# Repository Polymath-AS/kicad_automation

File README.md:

# KiCad 10 MCP Automation

This repository provides a reproducible Docker runtime for agent-driven KiCad work:

```text
Codex
  -> kicad-mcp-pro over Streamable HTTP
  -> KiCad 10 IPC / kipy
  -> pcbnew running under Xvfb

kicad-cli
  -> ERC, DRC, exports, validation
```

## Quick Start

After cloning, start the KiCad container and Codex together:

```powershell
.\tools\kicad-docker.ps1 start
```

The first run builds the Docker image, waits for the MCP endpoint, and then opens Codex. No token
setup is required. Docker Desktop must be installed and running.

Running plain `codex` is also safe: the KiCad MCP server is optional during Codex startup, so an
unavailable container no longer prevents the session from opening. Start the container and open a
new Codex session when you need KiCad tools.

## Build

```powershell
docker compose build
```

The image pins:

- `ghcr.io/inti-cmnb/kicad10_auto:1.9.0`, which ships KiCad `10.0.4` and the KiCad automation tool bundle.
- `kicad-mcp-pro==3.34.0`, installed in `/opt/kicad-mcp-pro`.

## Run

```powershell
docker compose up kicad
```

By default this opens `tests/fixtures/kicad-project/minimal.kicad_pcb`. To run against another mounted project:

```powershell
$env:KICAD_ENTRYPOINT_PROJECT = "CAD/my-board/my-board.kicad_pcb"
docker compose up kicad
```

The project is mounted at `/workspace`. Runtime sockets and logs live under `/runtime`; KiCad config is under `/config`; caches are under `/cache`.

The PowerShell wrapper validates the selected project on the host before Compose starts. A
complete target must resolve to matching `.kicad_pro`, `.kicad_sch`, and `.kicad_pcb` files under
`-ProjectRoot`. The host project root is mounted at `/workspace`, so the same resolved target is
passed to KiCad as `/workspace/<relative-project-path>`. This catches a stale selection or a
different mount before Docker validation runs; it does not recreate missing projects.

For example, validate a project from the same host root used by the live service with:

```powershell
.\tools\kicad-docker.ps1 validate tests/fixtures/kicad-project/minimal --erc --drc
```

If Docker itself fails, the wrapper preserves sanitized Compose output under
`.kicad-automation/compose-failures/` and reports the failure class. Authentication tokens are
not written to those reports.

MCP Pro is published only to host loopback:

```text
http://127.0.0.1:3334/mcp
```

Codex reads the project-scoped `.codex/config.toml` only for a trusted project. Its static
Authorization header matches the non-secret development token used by Compose. The service is
published only on host loopback, and a missing service does not prevent Codex from starting.
Verify the connection with `codex mcp list` and the `/mcp` command in the Codex interface.

For automation, diagnostics, and tools that are not visible in a client's cached catalog, use the
checked-in MCP client instead of constructing HTTP requests by hand:

```powershell
.\tools\kicad-mcp.ps1 wait
.\tools\kicad-mcp.ps1 list
.\tools\kicad-mcp.ps1 schema pcb_get_board_summary
.\tools\kicad-mcp.ps1 call pcb_get_board_summary --arguments '{}'
```

`list` annotates the live response with stable backend/availability metadata. Use
`.\tools\kicad-mcp.ps1 catalog` for the complete discoverable superset, including tools that are
currently unavailable in a selected upstream operating mode. Discoverability does not grant write
permission.

`--arguments` also accepts `@path/to/arguments.json`, which avoids shell-quoting problems for
larger payloads. Connection settings can be overridden with `KICAD_MCP_URL` and
`KICAD_MCP_AUTH_TOKEN`.

Codex project config example:

```toml
[mcp_servers.kicad]
url = "http://127.0.0.1:3334/mcp"
http_headers = { Authorization = "Bearer kicad-automation-local-dev-token-change-me-2026" }
required = false
startup_timeout_sec = 60
tool_timeout_sec = 120
default_tools_approval_mode = "writes"
```

## Generate a Project

MCP Pro exposes `kicad_create_new_project` in the default write-enabled profile. Generate a
complete KiCad project directory under the mounted `/workspace`; do not create a PCB-only file:

```text
my-board/
  my-board.kicad_pro
  my-board.kicad_sch
  my-board.kicad_pcb
```

The current runtime opens a board before starting MCP so that live IPC is ready. Bootstrap a new
project while the service is running against the fixture or another existing board, then restart
the service against the generated board:

```powershell
.\tools\kicad-docker.ps1 up `
  -ProjectRoot "C:\Users\fnk\Documents\KiCad\Projects" `
  -Target "my-board/my-board.kicad_pcb"
```

The generated project remains in the mounted host directory. After restarting, use MCP Pro for
inspection/editing and `validate-kicad --erc --drc` before continuing.

## MCP Surface

Use KiCad MCP Pro tool names directly. The default `builder` profile exposes the live PCB
workflow, including:

`kicad_get_server_info`, `kicad_get_project_info`, `kicad_get_version`, `pcb_get_board_summary`,
`pcb_get_footprints`, `pcb_get_nets`, `pcb_get_tracks`, `pcb_get_shapes`,
`pcb_visual_qa`, `pcb_visual_review`, `pcb_visual_history`, `pcb_visual_get`,
`pcb_visual_compare`, `pcb_move_component`, `pcb_move_footprint`,
`pcb_route_trace`, and `pcb_save`.

For iterative visual review, capture with `pcb_visual_review`, browse with `pcb_visual_history`,
zoom retained SVGs with `pcb_visual_get`, and compare captures with `pcb_visual_compare`.
Captures return native PNG image content and keep all SVGs, PNGs, frozen source copies, and
hash/version manifests under the active project's `output/image-review/<review-id>/`.
Open `output/image-review/index.html` to see progress. Nothing is automatically pruned.
These tools write review artifacts, not the design. Explicitly `pcb_save` first for live changes;
use `board_path` and `expected_sha256` for isolated candidates. See the
[review loop, API, retention guarantees, and setup](docs/PCB_VISUAL_REVIEW.md).

The default profile is `builder` with `KICAD_MCP_OPERATING_MODE=write` and file-backed schematic
support. It exposes the stable project-building surface needed to create and inspect schematics,
synchronize and edit a live PCB, route, save, and run ERC/DRC without restarting the service.
Use `manufacturing` or another specialized upstream profile only for workflows outside that
design surface.

Schematic support is split deliberately:

- KiCad 10.0.4 does not provide a verified schematic-editor IPC surface. The official IPC
  documentation describes KiCad 9/10 IPC as GUI-only and PCB-oriented; the installed `kipy`
  schematic class is marked KiCad 11-only and is incompatible with the bundled KiCad 10
  protobufs. The runtime therefore does not start Eeschema as a false readiness signal.
- The default `builder` profile exposes MCP Pro's supported file-backed schematic tools with
  `KICAD_MCP_SCHEMATIC_MODE=file_backed`. Their responses identify `Source: file-backed`.
- `KICAD_MCP_SCHEMATIC_MODE=live` fails early with the exact unsupported-stack diagnosis. It is
  reserved for a future verified KiCad 11+ IPC configuration; it does not silently fall back to
  file editing.

The project-scoped Codex allowlist includes the supported file-backed schematic inspection tools;
restart Codex after changing the server profile so its tool catalog is refreshed.

The integration test records `liveSchematicContext`, `liveSchematicRead`, schematic tool
exposure, and the backend identified by the schematic read. Set
`KICAD_TEST_SCHEMATIC_LIVE=1` only when testing a stack that is expected to provide a real live
schematic document; the test fails if MCP reports a file-backed fallback.

The pinned KiCad 10 pad-to-pad regression is opt-in because upstream exposes
`route_from_pad_to_pad` only in experimental write mode. Run it against a disposable two-pad
project with `KICAD_MCP_OPERATING_MODE=experimental` and `KICAD_TEST_PAD_TO_PAD=1`;
`scripts/pad_to_pad_regression.py` resolves named pads, routes and saves them, reads the live board
back, checks net assignment, and runs DRC. It reports pre-existing fixture warnings separately
from unconnected-route failures.

## Validate

`kicad-cli` is the validation/export authority. The primary entry point is:

```powershell
docker compose run --rm kicad validate --project /workspace/tests/fixtures/kicad-project/minimal --erc --drc
docker compose run --rm kicad validate --project /workspace/CAD/my-board/my-board --all
```

The script supports ERC, DRC, Gerbers, drill files, schematic/PCB PDFs, and BOM export.
It emits a JSON result with separate ERC and DRC statuses, report paths, violation counts, the
captured `kicad-cli` log, and an overall status. `clean` is used only when both requested checks
ran and produced no violations. Missing project files, validator execution errors, and reported
ERC/DRC violations return distinct nonzero outcomes.

## Preferred KiCadRoutingTools placement and routing

The separate routing image exposes conservative placement refinement plus `route`, `diff`, and
`planes` as validated candidate jobs through CLI and MCP. After initial MCP placement, save the
unrouted board and use the candidate placer's bounded moves to improve routability. Lock
connectors, mounting parts, and RF/mechanical-critical parts, and provide reviewed placement
intent when available. KiCadRoutingTools is the preferred routing path; direct IPC traces remain
useful for previews and small reviewed fixes. The candidate service reads the source project
through a read-only mount, preserves the original rules for ERC/DRC, and never automatically
overwrites the live board.

Reviewed additive-track and placement candidates can be promoted explicitly through
`scripts/kicad_live_promotion.py` and `scripts/kicad_live_placement.py`. Promotion requires stale
source checks, save/reopen/readback, and post-mutation validation. Unsupported vias/removals and
unverifiable rollback fail closed; candidate generation itself remains non-mutating.

```powershell
.\tools\kicad-routing.cmd build
.\tools\kicad-routing.cmd doctor
.\tools\kicad-routing.cmd run routing-plans/smoke.json
```

The smoke fixture is expected to return `needs_review`: routing resolves its missing connection,
but two pre-existing footprint identifier warnings remain. Non-clean candidates return exit 1.
See [the detailed integration guide and remaining milestones](docs/KICAD_ROUTING_TOOLS.md)
for installation, MCP configuration, plans, evidence, review, limitations and tests.

## Test

```powershell
docker compose run --rm test
```

The integration path verifies KiCad 10.x, Xvfb, `DISPLAY`, pcbnew launch, IPC socket creation,
MCP Pro startup, MCP tool discovery, live PCB queries before and after save, project diagnostics,
schematic capability evidence when a schematic profile is selected, and separate clean ERC/DRC
results. It does not treat an Eeschema process that merely stays alive as proof of schematic IPC.

PowerShell convenience wrapper:

```powershell
.\tools\kicad-docker.ps1 build
.\tools\kicad-docker.ps1 test
.\tools\kicad-docker.ps1 validate tests/fixtures/kicad-project/minimal --erc --drc
```

On Windows hosts that enforce a restrictive PowerShell execution policy, use the checked-in
launchers instead of changing machine or user policy:

```bat
tools\kicad-docker.cmd start
tools\kicad-docker.cmd validate tests/fixtures/kicad-project/minimal --erc --drc
tools\kicad-mcp.cmd call pcb_get_board_summary
```

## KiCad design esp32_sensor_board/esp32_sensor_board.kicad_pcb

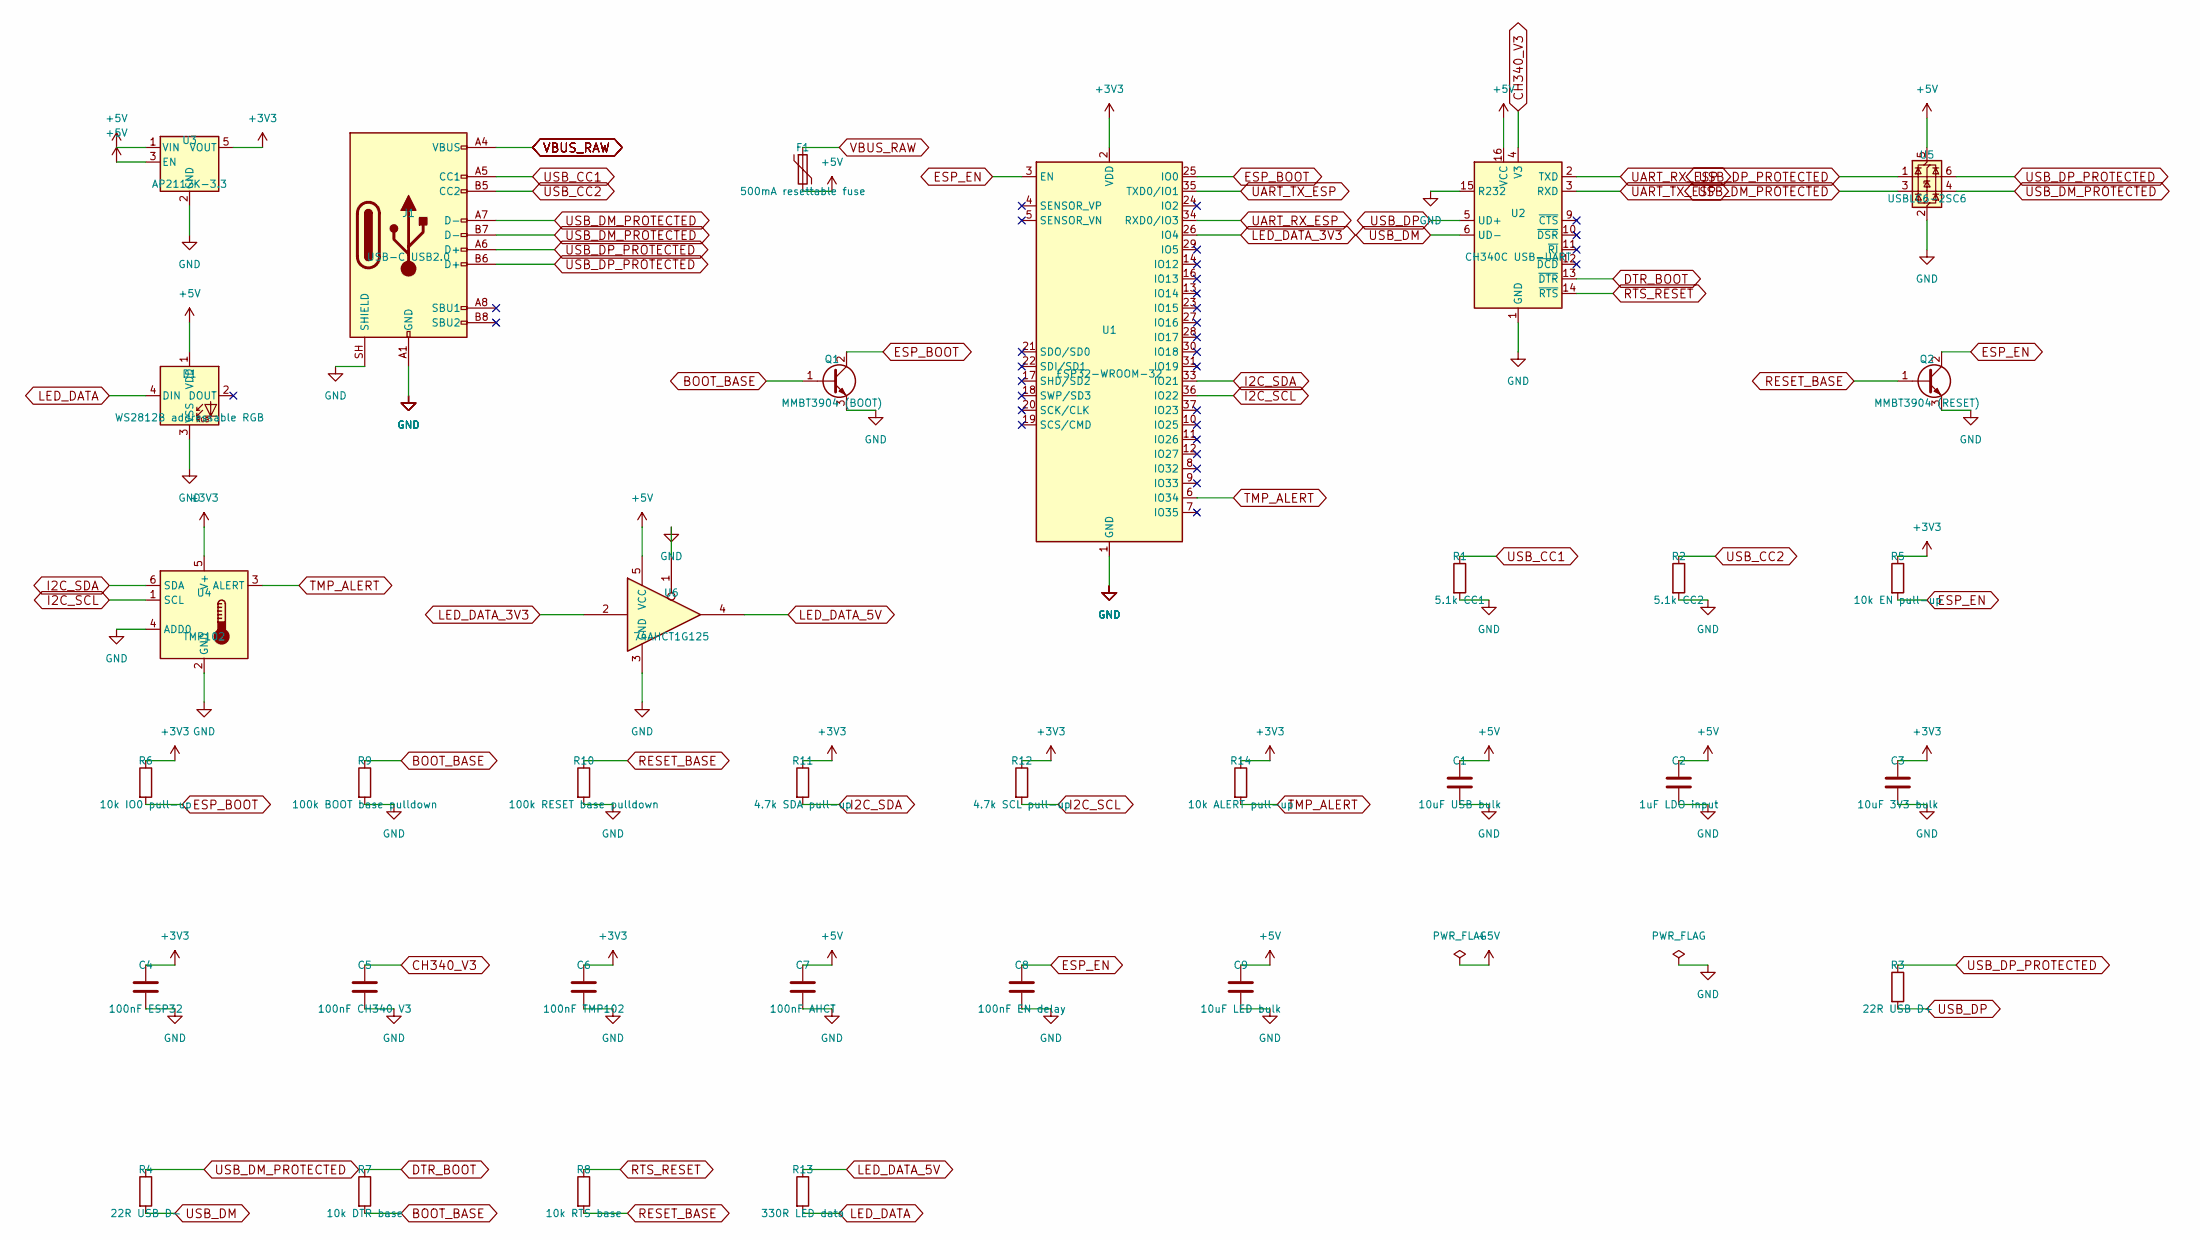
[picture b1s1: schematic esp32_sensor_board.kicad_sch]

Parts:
C1: 10uF USB bulk; C_1206_3216Metric
C2: 1uF LDO input; C_0603_1608Metric
C3: 10uF 3V3 bulk; C_1206_3216Metric
C4: 100nF ESP32; C_0603_1608Metric
C5: 100nF CH340 V3; C_0603_1608Metric
C6: 100nF TMP102; C_0603_1608Metric
C7: 100nF AHCT; C_0603_1608Metric
C8: 100nF EN delay; C_0603_1608Metric
C9: 10uF LED bulk; C_1206_3216Metric
D1: WS2812B addressable RGB; LED_WS2812B_PLCC4_5.0x5.0mm_P3.2mm
F1: 500mA resettable fuse; Fuse_1206_3216Metric
J1: USB-C USB2.0; USB_C_Receptacle_GCT_USB4105-xx-A_16P_TopMnt_Horizontal
Q1: MMBT3904 (BOOT); SOT-23
Q2: MMBT3904 (RESET); SOT-23
R1: 5.1k CC1; R_0603_1608Metric
R2: 5.1k CC2; R_0603_1608Metric
R3: 22R USB D+; R_0603_1608Metric
R4: 22R USB D-; R_0603_1608Metric
R5: 10k EN pull-up; R_0603_1608Metric
R6: 10k IO0 pull-up; R_0603_1608Metric
R7: 10k DTR base; R_0603_1608Metric
R8: 10k RTS base; R_0603_1608Metric
R9: 100k BOOT base pulldown; R_0603_1608Metric
R10: 100k RESET base pulldown; R_0603_1608Metric
R11: 4.7k SDA pull-up; R_0603_1608Metric
R12: 4.7k SCL pull-up; R_0603_1608Metric
R13: 330R LED data; R_0603_1608Metric
R14: 10k ALERT pull-up; R_0603_1608Metric
U1: ESP32-WROOM-32
U2: CH340C USB-UART; SOIC-16_3.9x9.9mm_P1.27mm
U3: AP2112K-3.3; SOT-23-5
U4: TMP102; SOT-563
U5: USBLC6-2SC6; SOT-23-6
U6: 74AHCT1G125; SOT-23-5

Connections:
+3V3: C3.1, C4.1, C6.1, R5.1, R6.1, R11.1, R12.1, R14.1, U1.2 (VDD), U3.5 (VOUT), U4.5 (V+)
+5V: C1.1, C2.1, C7.1, C9.1, D1.1 (VDD), F1.2, U2.16 (VCC), U3.1 (VIN), U3.3 (EN), U5.5 (VBUS), U6.5 (VCC)
BOOT_BASE: Q1.1 (B), R7.2, R9.1
CH340_V3: C5.1, U2.4 (V3)
DTR_BOOT: R7.1, U2.13 (~DTR)
ESP_BOOT: Q1.2 (C), R6.2, U1.25 (IO0)
ESP_EN: C8.1, Q2.2 (C), R5.2, U1.3 (EN)
GND: C1.2, C2.2, C3.2, C4.2, C5.2, C6.2, C7.2, C8.2, C9.2, D1.3 (VSS), J1.A1 (GND), J1.A12 (GND), J1.B1 (GND), J1.B12 (GND), J1.SH (SHIELD), Q1.3 (E), Q2.3 (E), R1.2, R2.2, R9.2, R10.2, U1.1 (GND), U1.15 (GND), U1.38 (GND), U1.39 (GND), U2.1 (GND), U2.15 (R232), U3.2 (GND), U4.2 (GND), U4.4 (ADD0), U5.2 (GND), U6.1, U6.3 (GND)
I2C_SCL: R12.2, U1.36 (IO22), U4.1 (SCL)
I2C_SDA: R11.2, U1.33 (IO21), U4.6 (SDA)
LED_DATA: D1.4 (DIN), R13.2
LED_DATA_3V3: U1.26 (IO4), U6.2
LED_DATA_5V: R13.1, U6.4
RESET_BASE: Q2.1 (B), R8.2, R10.1
RTS_RESET: R8.1, U2.14 (~RTS)
TMP_ALERT: R14.2, U1.6 (IO34), U4.3 (ALERT)
UART_RX_ESP: U1.34 (RXD0/IO3), U2.2 (TXD)
UART_TX_ESP: U1.35 (TXD0/IO1), U2.3 (RXD)
USB_CC1: J1.A5 (CC1), R1.1
USB_CC2: J1.B5 (CC2), R2.1
USB_DM: R4.2, U2.6 (UD-)
USB_DM_PROTECTED: J1.A7 (D-), J1.B7 (D-), R4.1, U5.3 (I/O2), U5.4 (I/O2)
USB_DP: R3.2, U2.5 (UD+)
USB_DP_PROTECTED: J1.A6 (D+), J1.B6 (D+), R3.1, U5.1 (I/O1), U5.6 (I/O1)
VBUS_RAW: F1.1, J1.A4 (VBUS), J1.A9 (VBUS), J1.B4 (VBUS), J1.B9 (VBUS)

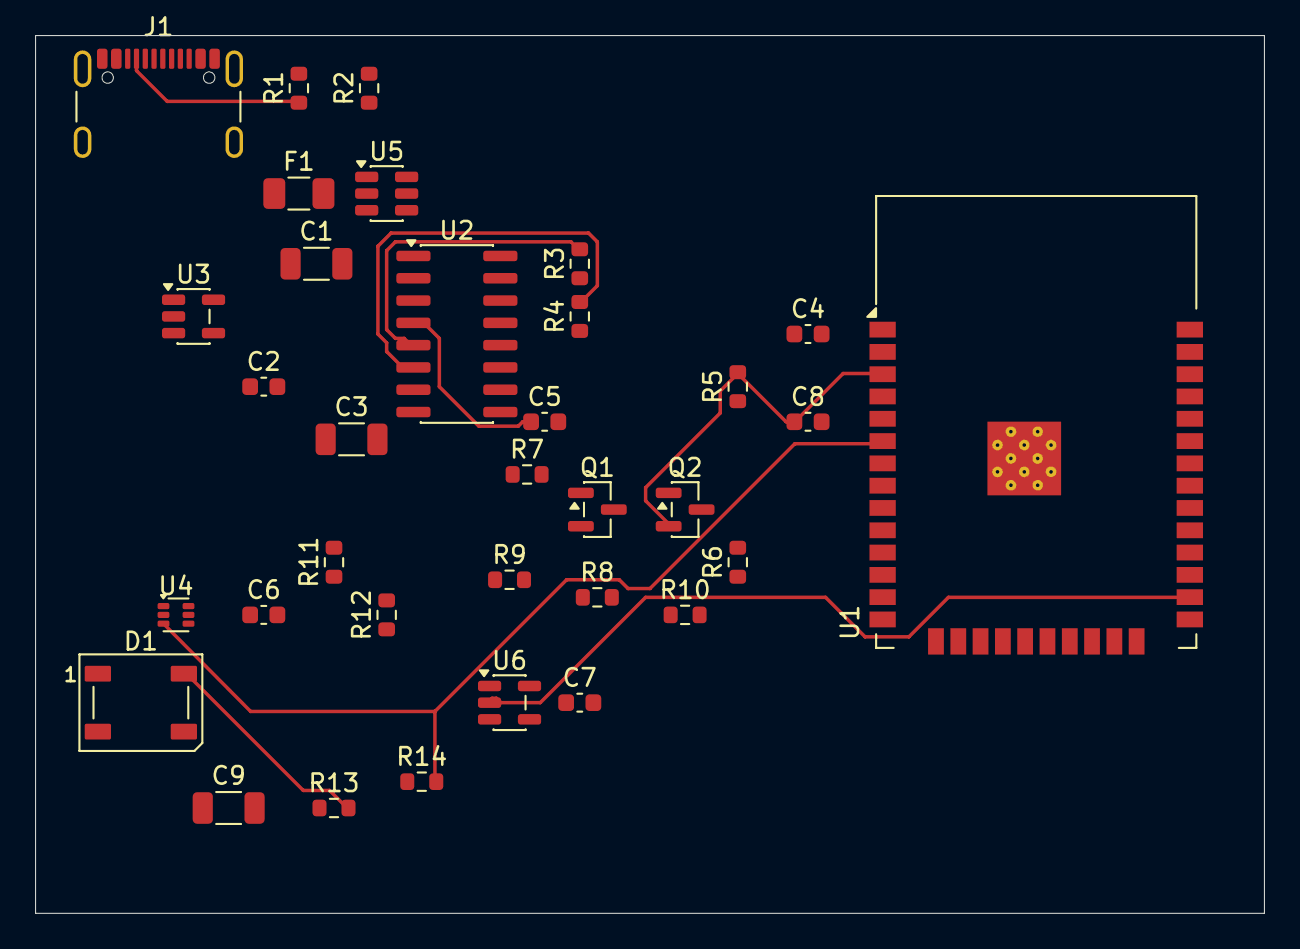
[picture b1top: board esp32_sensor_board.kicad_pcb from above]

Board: 2 copper layers, 70.0 x 50.0 mm, 34 parts (0 on the bottom side), 25 nets.
